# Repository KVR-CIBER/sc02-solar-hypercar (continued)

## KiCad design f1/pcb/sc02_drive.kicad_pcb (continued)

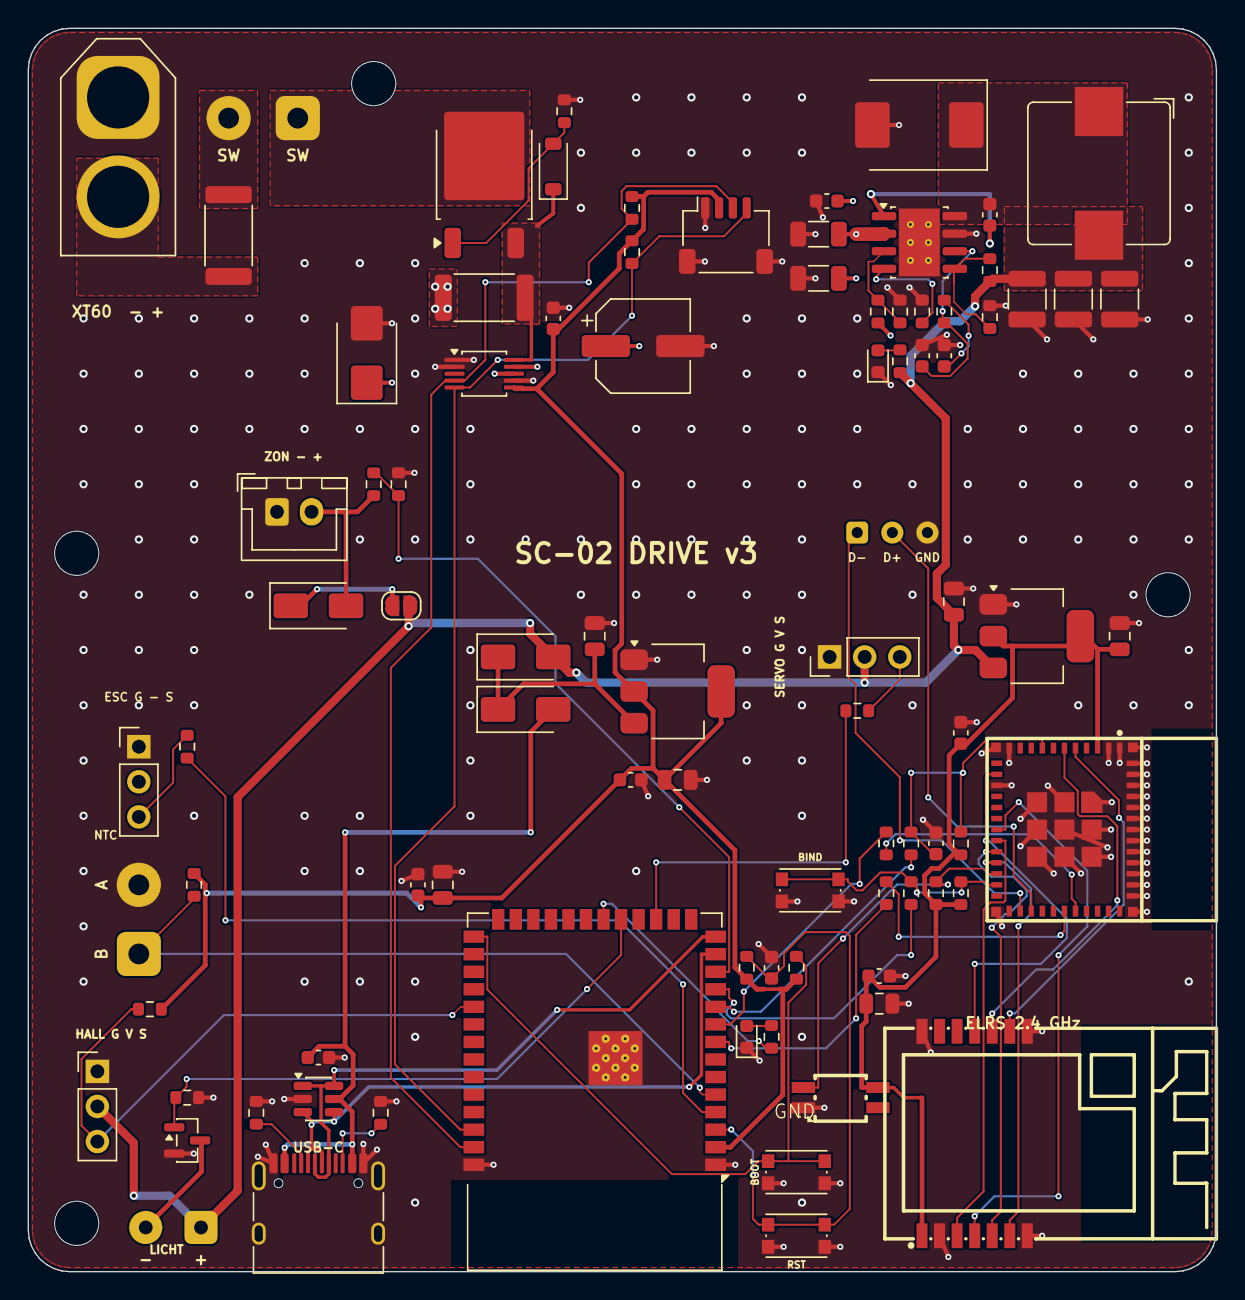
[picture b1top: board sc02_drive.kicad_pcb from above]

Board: 4 copper layers, 86.0 x 90.0 mm, 94 parts (0 on the bottom side), 59 nets.

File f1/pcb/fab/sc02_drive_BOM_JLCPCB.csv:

Comment,Designator,Footprint,Quantity,MPN / note,LCSC Part #
XT60,J1,AMASS_XT60-M_1x02_P7.20mm_Vertical,1,"AMASS XT60-M (male, vertical): the LiPo plugs in from above",C98733
10A,F1,R_2512_6332Metric,1,"2410FA-10A (fast 10 A, 2410 body on 2512 pads)",C2838934
SCHAKELAAR,J11,SolderWire_2pad_P5mm_SW,1,solder pads for the power switch (mounted from below in the 6.2 mm hole),"(solder pads, no part)"
AOD4185,Q1,TO-252-2,1,"AOD4185 (P-MOSFET 40 V 40 A, reverse polarity)",C400894
10k,"R1,R11,R12,R19,R31,R32",R_0603_1608Metric,6,0603 10k 1%,C25804
BZT52C15,D2,D_SOD-123,1,BZT52C15 (gate clamp),C173427
2m,RS1,R_2512_6332Metric,1,2512 2 mOhm 2 W current shunt,C160590
SMBJ15CA,D1,D_SMB,1,SMBJ15CA,C78410
100u 25V,C1,CP_Elec_6.3x7.7,1,100uF 25V 6.3x7.7 alu,C72477
INA226,U6,TSSOP-10_3x3mm_P0.5mm,1,INA226AIDGSR (0x40),C49851
100n,"C2,C7,C8,C16,C18,C32,C34",C_0603_1608Metric,7,0603 100n X7R ceramic,C14663
TPS54560B,U1,Texas_R-PDSO-G8_EP2.95x4.9mm_Mask2.4x3.1mm_ThermalVias,1,TPS54560BDDAR,C1850354
10u 25V,"C5,C6",C_1206_3216Metric,2,1206 10u 25V X5R ceramic,C9807
442k,R4,R_0603_1608Metric,1,0603 442k 1%,C23175
90.9k,R5,R_0603_1608Metric,1,0603 90.9k 1%,C23129
243k,R6,R_0603_1608Metric,1,0603 243k 1%,C23351
6.8u,L1,L_Bourns_SRP1038C_10.0x10.0mm,1,"Bourns SRP1038C-6R8M (6.8 uH, >= 8 A)",C20804570
B560C,D4,D_SMC,1,B560C (5 A 60 V Schottky),C85100
47u 10V,"C9,C10,C11",C_1210_3225Metric,3,1210 47u 10V X5R ceramic,C84494
53.6k,R7,R_0603_1608Metric,1,0603 53.6k 1%,C23074
10.2k,R8,R_0603_1608Metric,1,0603 10.2k 1%,C22772
16.9k,R9,R_0603_1608Metric,1,0603 16.9k 1%,C25954
4n7,C12,C_0603_1608Metric,1,0603 4n7 X5R ceramic,C53987
47p,C13,C_0603_1608Metric,1,0603 47p X7R ceramic,C1671
groen 5V,D5,LED_0603_1608Metric,1,LED 0603 green,C12624
2k2,R10,R_0603_1608Metric,1,0603 2k2 1%,C4190
I2C,J7,JST_SH_SM04B-SRSS-TB_1x04-1MP_P1.00mm_Horizontal,1,JST SM04B-SRSS-TB (Qwiic / STEMMA QT),C160404
4k7,"R24,R25",R_0603_1608Metric,2,0603 4k7 1%,C23162
ESC,J2,PinHeader_1x03_P2.54mm_Vertical,1,"1x3 pin header 2.54 (ESC signal lead: black GND, red BEC NOT used, white/yellow signal)",C49257
100,"R20,R18,R29,R30",R_0603_1608Metric,4,0603 100 1%,C22775
ESC TEMP,J3,SolderWire_2pad_P5mm_M,1,solder pads: 10k NTC glued on the ESC / motor can (temperature for the boost limit),"(solder pads, no part)"
10k,R21,R_0603_1608Metric,1,0603 10k 1% (NTC divider),C25804
SS14,"D6,D7",D_SMA,2,SS14,C2480
AMS1117-3.3,U2,SOT-223-3_TabPin2,1,AMS1117-3.3,C6186
10u,"C14,C30,C33",C_0805_2012Metric,3,0805 10u X5R ceramic,C15850
22u,"C15,C17,C31",C_0805_2012Metric,3,0805 22u X5R ceramic,C29277
ESP32-S3-WROOM-1-N16R8,U3,ESP32-S3-WROOM-1,1,ESP32-S3-WROOM-1-N16R8,C2913202
1u,"C19,C29,C35",C_0603_1608Metric,3,0603 1u X5R ceramic,C15849
RESET,SW1,SW_Push_1P1T_NO_CK_KMR2,1,CK KMR221G (4.2x2.8 tact),C72443
BOOT,SW2,SW_Push_1P1T_NO_CK_KMR2,1,CK KMR221G (4.2x2.8 tact) - also the race-mode button,C72443
geel ESP,D8,LED_0603_1608Metric,1,LED 0603 yellow,C2287
1k,R13,R_0603_1608Metric,1,0603 1k 1%,C21190
USB-C,J8,USB_C_Receptacle_HRO_TYPE-C-31-M-12,1,HRO TYPE-C-31-M-12 (board edge),C165948
5k1,"R27,R28",R_0603_1608Metric,2,0603 5k1 1%,C23186
USBLC6-2SC6,U10,SOT-23-6,1,USBLC6-2SC6,C2687116
HALL,J5,PinHeader_1x03_P2.54mm_Vertical,1,"1x3 pin header 2.54 (A3144: GND, 5 V, out)",C49257
ZONNEPANEEL,J6,JST_XH_B2B-XH-A_1x02_P2.50mm_Vertical,1,JST XH 2-pin (B2B-XH-A): plug the solar panel in (5 V 1 W),C158012
100k,"R22,R26",R_0603_1608Metric,2,0603 100k 1%,C25803
33k,R23,R_0603_1608Metric,1,0603 33k 1%,C4216
SS14,D9,D_SMA,1,SS14 (solar -> 5 V),C2480
ZON>5V,JP1,SolderJumper-2_P1.3mm_Open_RoundedPad1.0x1.5mm,1,solder jumper (open): solar panel feeds the 5 V rail,"(solder jumper, no part)"
LICHTEN,J10,SolderWire_2pad_P4mm_S,1,"solder pads, LED lights 5 V (with their own resistors), low-side switched","(solder pads, no part)"
AO3400A,Q4,SOT-23,1,AO3400A,C20917
ESP32-C3-MINI-1-N4,U11,WIFIM-SMD_ESP32-C3-MINI-1,1,"ESP32-C3-MINI-1-N4 (ELRS receiver MCU, flash ""Generic C3 2400"")",C2838502
E28-2G4M12S,U12,WIRELM-SMD_E28-2G4M12S,1,"Ebyte E28-2G4M12S (SX1280 2.4 GHz, 12.5 dBm, PCB antenna)",C411310
AMS1117-3.3,U13,SOT-223-3_TabPin2,1,AMS1117-3.3 (receiver supply),C6186
10k,R33,R_0603_1608Metric,1,0603 10k (IO8 strapping pin high at boot),C25804
1k,R34,R_0603_1608Metric,1,0603 1k (S3 can reset the receiver),C21190
1k,R35,R_0603_1608Metric,1,0603 1k (S3 can start the receiver bootloader),C21190
BIND,SW3,SW_Push_1P1T_NO_CK_KMR2,1,CK KMR221G: ELRS bind / bootloader button,C72443
SK6812MINI-E,D10,LED-SMD_4P-L3.2-W2.8-LS5.9_SK6812MINI-E,1,"SK6812MINI-E (ELRS status LED, RGB)",C5149201
RX USB,J12,Pads_RX_USB,1,test pads: USB D-/D+/GND of the receiver C3 (first flash),"(test pads, no part)"
